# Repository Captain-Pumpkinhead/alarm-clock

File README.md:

# alarm-clock
My code and PCB designs for my alarm clock project.

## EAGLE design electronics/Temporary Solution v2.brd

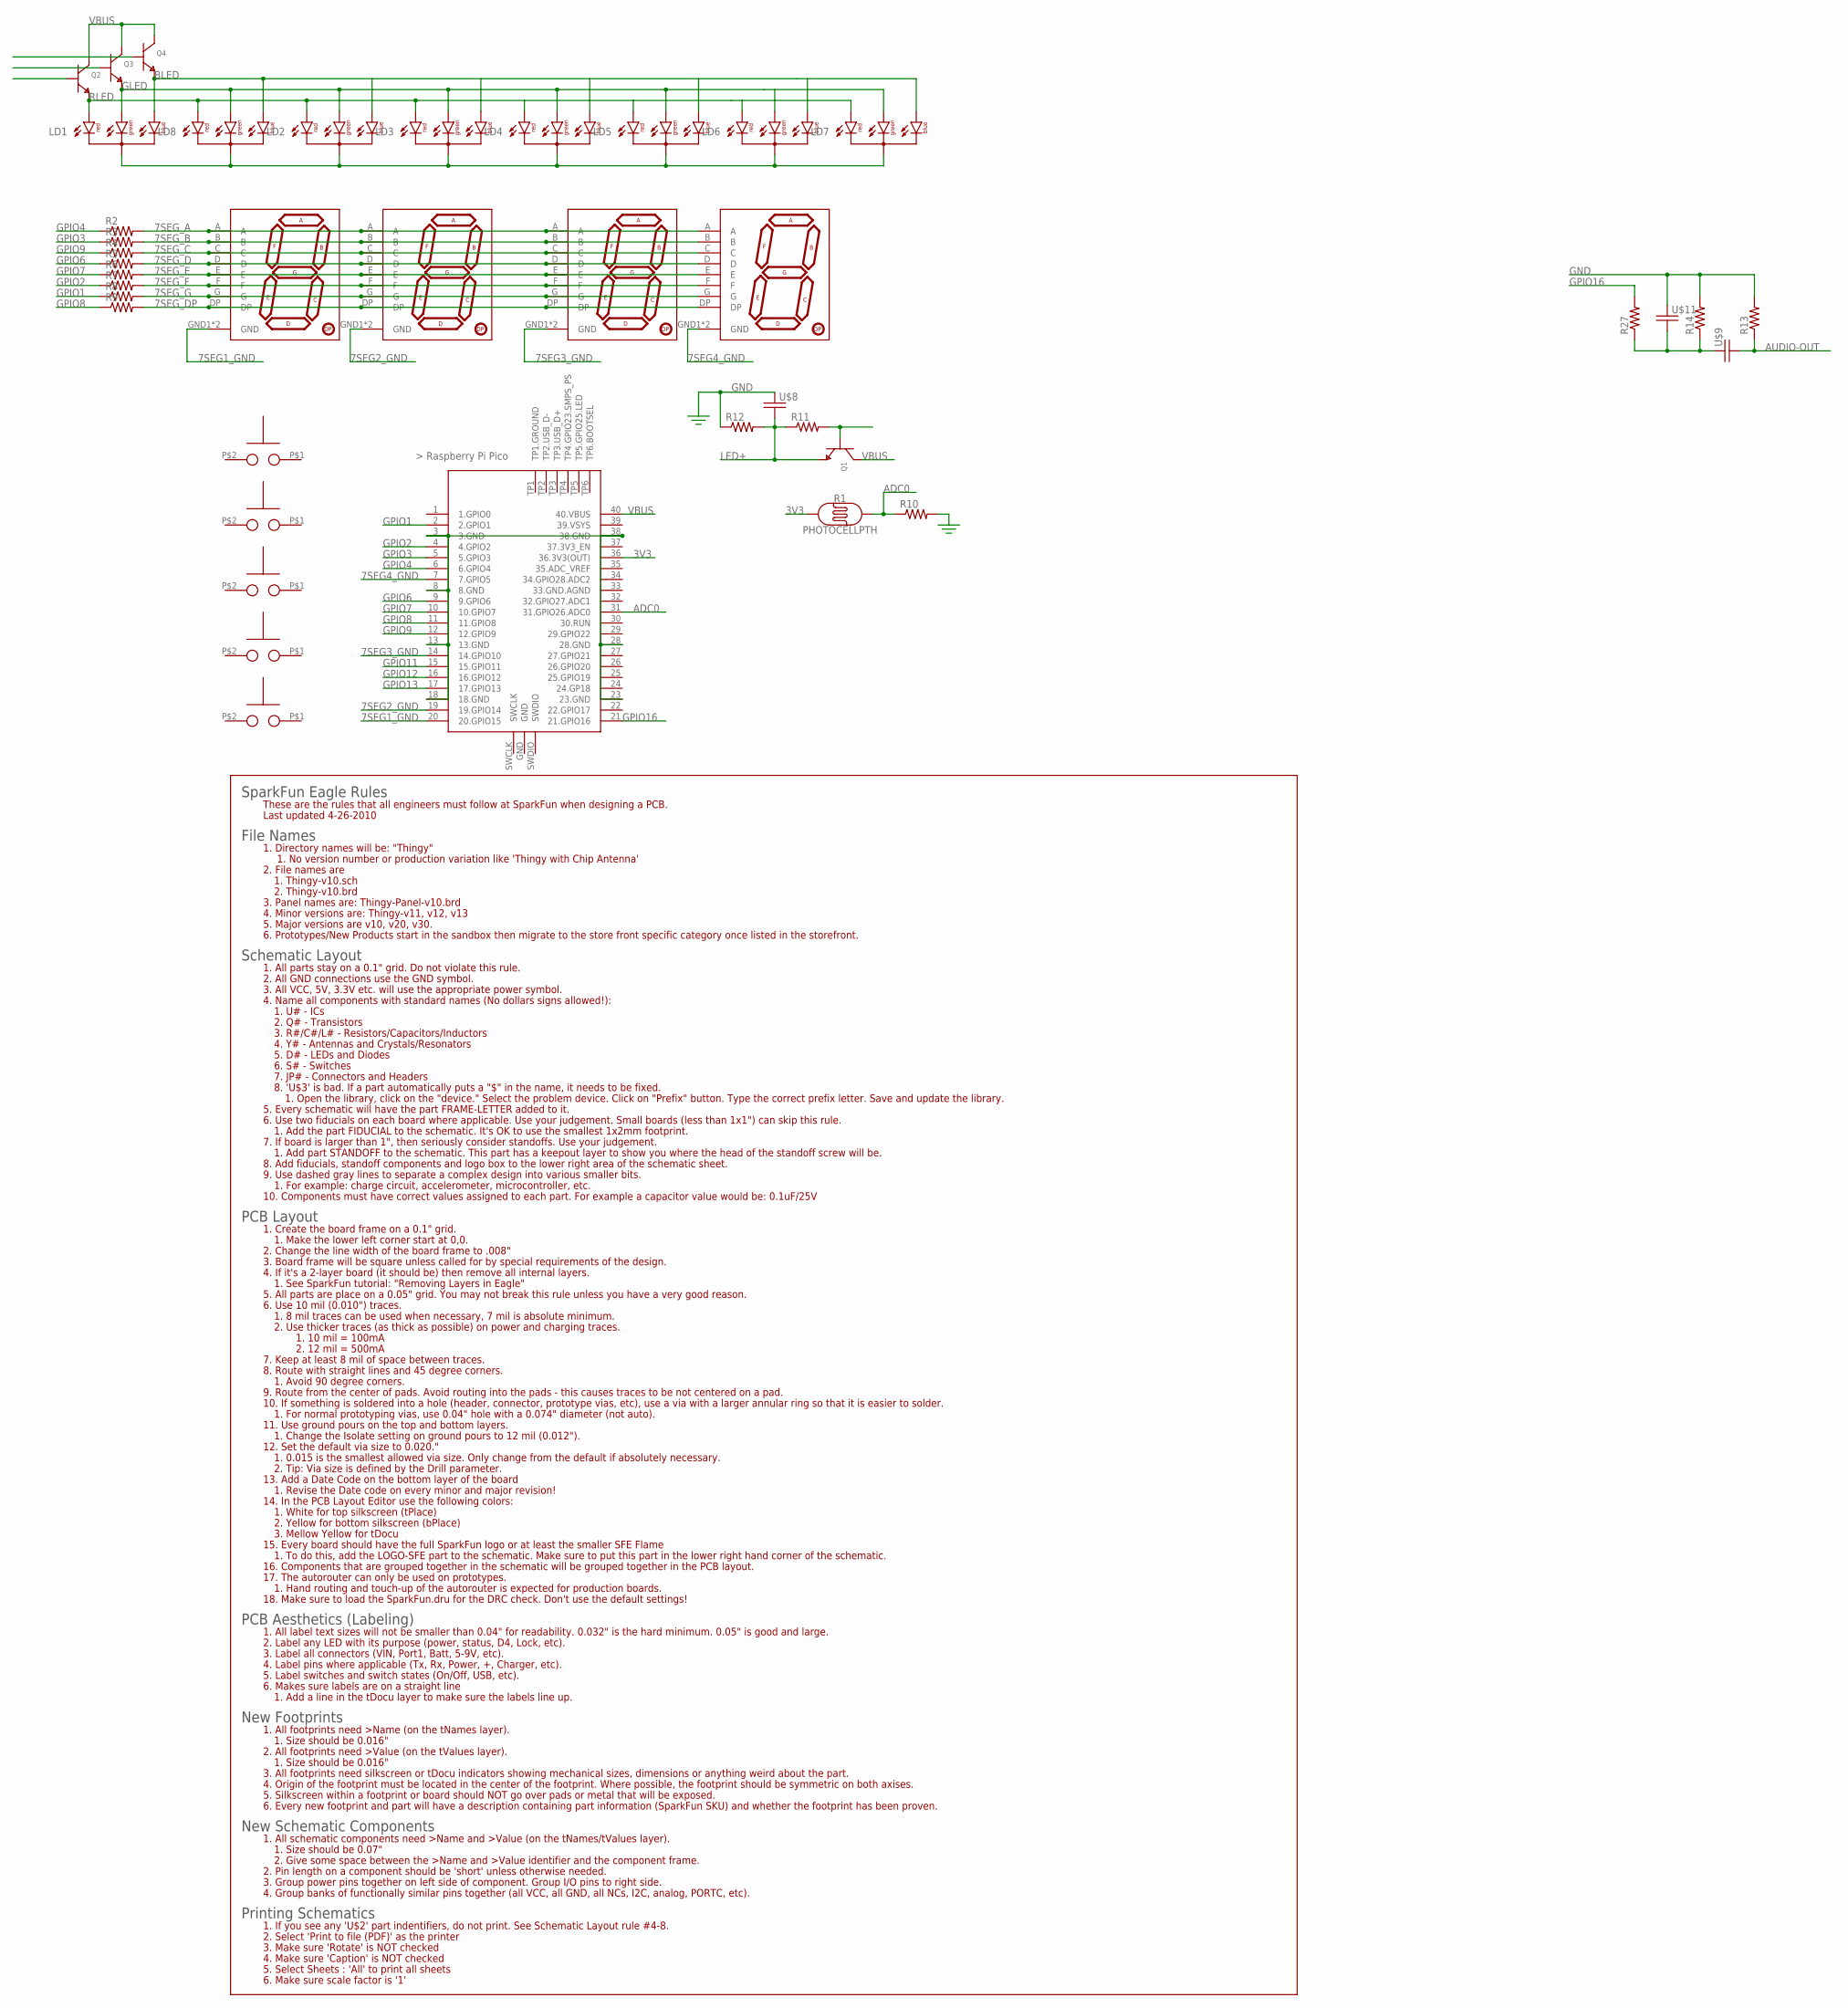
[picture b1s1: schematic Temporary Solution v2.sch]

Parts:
D1, D2, D3, D4: 7SEGMENT-1DIGIT
LD1, LD2, LD3, LD4, LD5, LD6, LD7, LD8: LED_RGB
Q1, Q2, Q3, Q4: BJT_NPN_EBC_2N2222; NPN_EBC_.1IN
R1: PHOTOCELLPTH; PHOTOCELL
R2, R3, R4, R5, R6, R7, R8, R9, R10, R11, R12, R13, R14, R27: R-US_0207/7; 0207/7
U$2: RASPBERRY_PI_PICO_TH
U$3, U$4, U$5, U$6, U$7: BUTTONPUSHBUTTON_2-PIN; BUTTON_PUSHBUTTON_2-PIN
U$8, U$9, U$11: CAPACITOR-NONPOLARIZEDTH-CERAMIC; CAPACITOR-CERAMIC

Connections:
3V3: R1.1, U$2.36 (36.3V3(OUT))
7SEG1_GND: D1.GND1 (GND), D1.GND2 (GND), U$2.20 (20.GPIO15)
7SEG2_GND: D2.GND1 (GND), D2.GND2 (GND), U$2.19 (19.GPIO14)
7SEG3_GND: D3.GND1 (GND), D3.GND2 (GND), U$2.14 (14.GPIO10)
7SEG4_GND: D4.GND1 (GND), D4.GND2 (GND), U$2.7 (7.GPIO5)
7SEG_A: D1.A, D2.A, D3.A, D4.A, R2.2
7SEG_B: D1.B, D2.B, D3.B, D4.B, R3.2
7SEG_C: D1.C, D2.C, D3.C, D4.C, R4.2
7SEG_D: D1.D, D2.D, D3.D, D4.D, R5.2
7SEG_DP: D1.DP, D2.DP, D3.DP, D4.DP, R9.2
7SEG_E: D1.E, D2.E, D3.E, D4.E, R6.2
7SEG_F: D1.F, D2.F, D3.F, D4.F, R7.2
7SEG_G: D1.G, D2.G, D3.G, D4.G, R8.2
ADC0: R1.2, R10.1, U$2.31 (31.GPIO26.ADC0)
AUDIO-OUT: R13.1, U$9.2
BLED: LD1.BLUE, LD2.BLUE, LD3.BLUE, LD4.BLUE, LD5.BLUE, LD6.BLUE, LD7.BLUE, LD8.BLUE, Q4.3 (E)
GLED: LD1.GRN (GREEN), LD2.GRN (GREEN), LD3.GRN (GREEN), LD4.GRN (GREEN), LD5.GRN (GREEN), LD6.GRN (GREEN), LD7.GRN (GREEN), LD8.GRN (GREEN), Q3.3 (E)
GND: R10.2, R12.1, R13.2, R14.2, U$2.3 (3.GND), U$2.8 (8.GND), U$2.13 (13.GND), U$2.18 (18.GND), U$2.23 (23.GND), U$2.28 (28.GND), U$2.38 (38.GND), U$8.1, U$11.1
GPIO1: R8.1, U$2.2 (2.GPIO1)
GPIO2: R7.1, U$2.4 (4.GPIO2)
GPIO3: R3.1, U$2.5 (5.GPIO3)
GPIO4: R2.1, U$2.6 (6.GPIO4)
GPIO6: R5.1, U$2.9 (9.GPIO6)
GPIO7: R6.1, U$2.10 (10.GPIO7)
GPIO8: R9.1, U$2.11 (11.GPIO8)
GPIO9: R4.1, U$2.12 (12.GPIO9)
GPIO11: U$2.15 (15.GPIO11)
GPIO12: U$2.16 (16.GPIO12)
GPIO13: U$2.17 (17.GPIO13)
GPIO16: R27.2, U$2.21 (21.GPIO16)
LED+: Q1.3 (E), R11.1, R12.2, U$8.2
unnamed: Q1.1 (B), R11.2
unnamed: LD1.GND, LD2.GND, LD3.GND, LD4.GND, LD5.GND, LD6.GND, LD7.GND, LD8.GND
unnamed: R14.1, R27.1, U$9.1, U$11.2
RLED: LD1.RED, LD2.RED, LD3.RED, LD4.RED, LD5.RED, LD6.RED, LD7.RED, LD8.RED, Q2.3 (E)
VBUS: Q1.2 (C), Q2.2 (C), Q3.2 (C), Q4.2 (C), U$2.40 (40.VBUS)

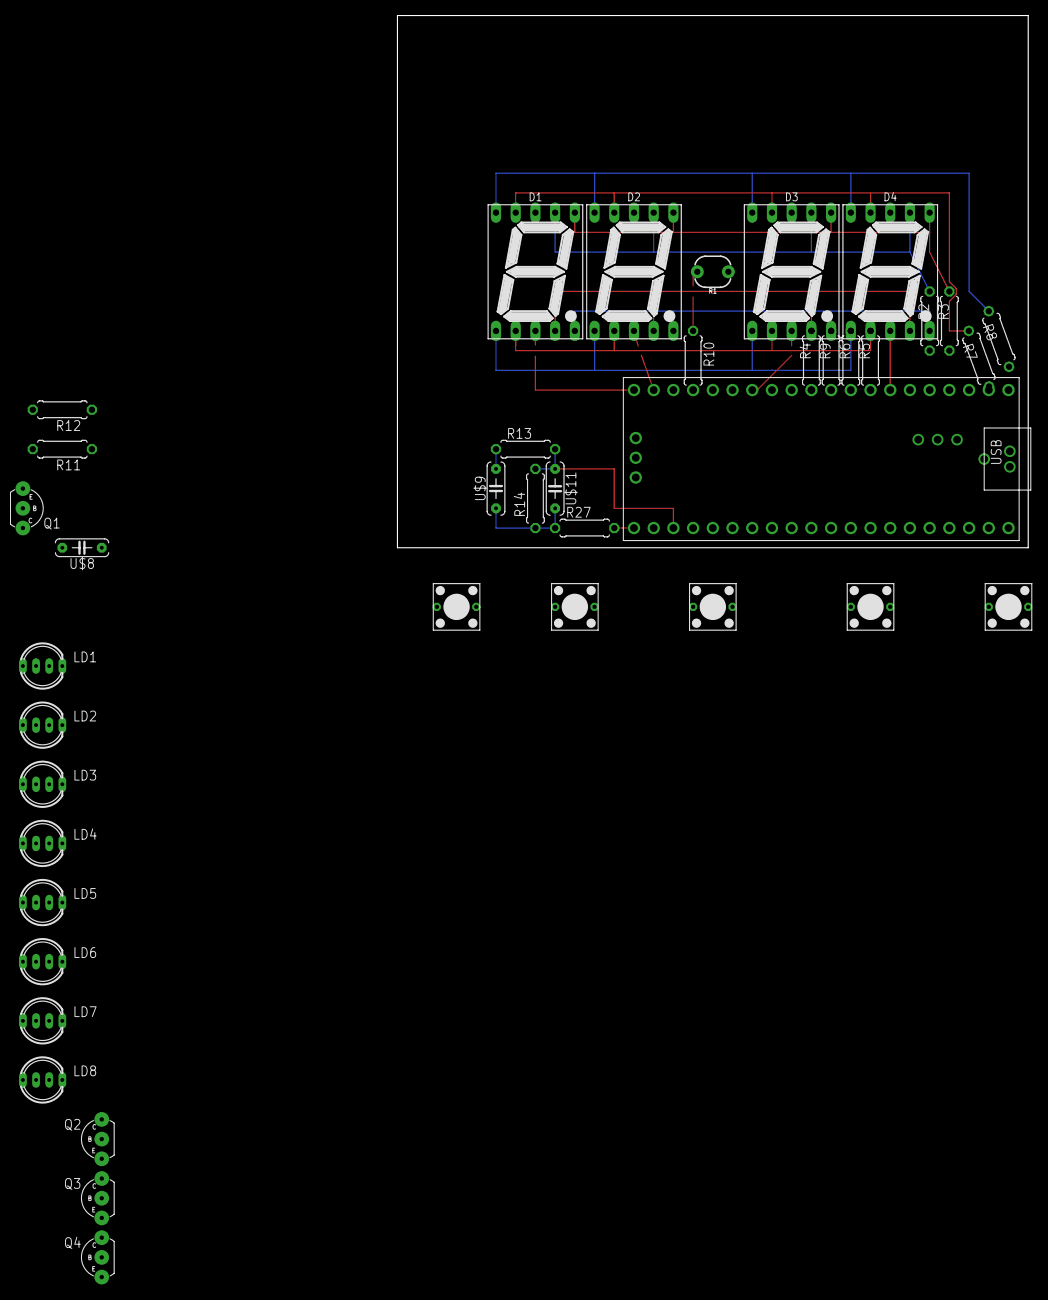
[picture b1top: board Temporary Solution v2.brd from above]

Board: 2 copper layers, 81.3 x 68.6 mm, 40 parts (0 on the bottom side), 33 nets.

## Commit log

2022-12-09 Initial Commit 2022.12.08
    I've worked on this project offline for a while. Here is my first commit to the git repo.

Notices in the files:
parts and their libraries:
SparkFun-Sensors: Licensing: Creative Commons ShareAlike 4.0 International - https://creativecommons.org/licenses/by-sa/4.0
